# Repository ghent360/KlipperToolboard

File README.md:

# Huvud 3D Printer toolhead board
This is a modified version of the KilipperBoard started by bondus(https://github.com/bondus/KlipperToolboard). The goal is to make the board as cheap as possible. Removed the CAN interface, switched to RP4020 MCU since it is more available. Added extra IO pins for LEDs or other sensors.
# Original author words
A very small 3D printer board for use on a direct drive toolhead. It is designed to be used with Klipper firmware. Klipper has the awesome feature to be able to use multiple MCUs connected to the host over a (relatively) high latency connection.

Features: 
* One TMC2209 stepper driver for the extruder
* Three MOSFETs for fans
* One big MOSFET for the hotend heater
* Two thermistor inputs
* ADXL345 accelerometer for resonance testing
* Support for 3 endstops
* 3 extra I/O pins for RGB LEDs or other functions
* RP4020 Dual core 133MHz 32bit ARM MCU
* USB, for flashing firmware

Main power is 12-24V. 24V is preferred to keep the currents low

All done in KiCad and open source. 

If you are interesting in helping out, testing or eventually using this board feel free to contact me at ghent360@iqury.us.

### Documentation

* [Pinout and hook up](doc/pinout.md)
* [Klipper configuration](doc/klipper.md)
* [Prototype versions of the board](doc/versions.md)

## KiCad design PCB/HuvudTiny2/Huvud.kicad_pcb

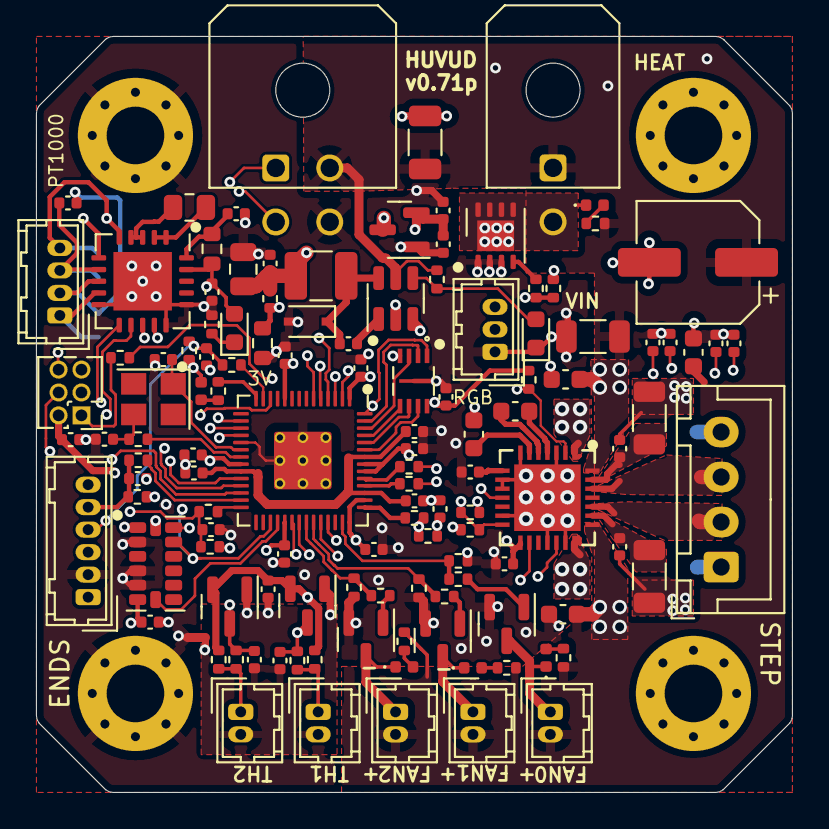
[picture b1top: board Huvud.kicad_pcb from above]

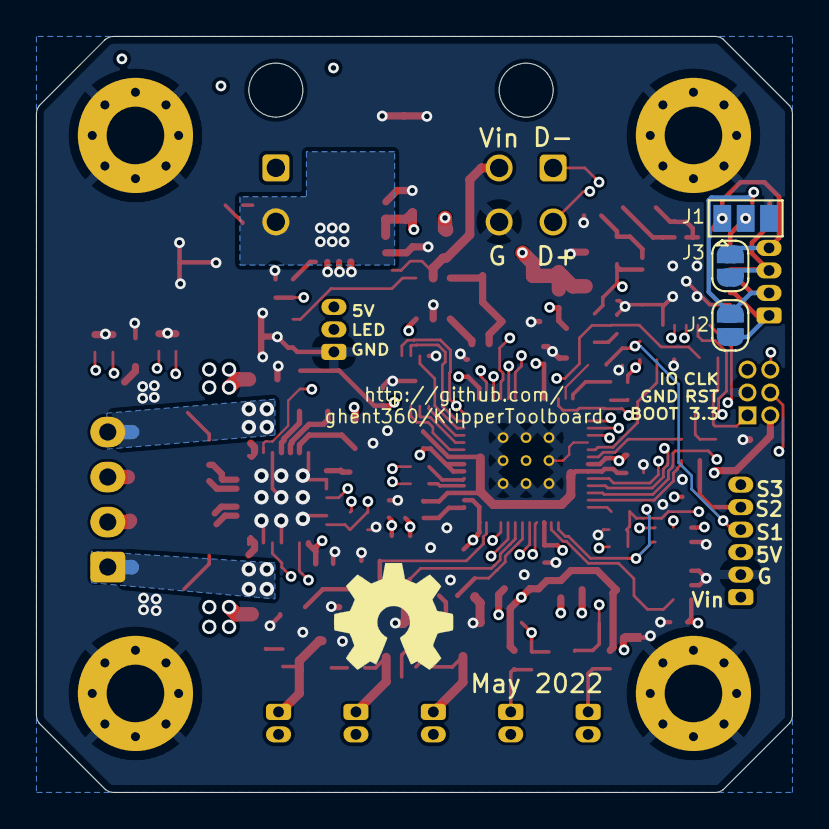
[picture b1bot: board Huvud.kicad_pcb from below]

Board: 4 copper layers, 42.0 x 42.0 mm, 129 parts (4 on the bottom side), 88 nets.

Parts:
C1, C2, C9, C10, C11, C19, C23, C24, C25, C27, C30, C31, C35, C37, C38, C39, C40, C41, C42, C43, C45: 0.1uF; C_0402_1005Metric
C3, C6, C7, C16: 0.1uF/35V; C_0603_1608Metric
C4, C17, C33, C34: 4.7uF; C_0402_1005Metric
C5: 22nf/50V; C_0603_1608Metric
C8: 100uF/35V; CP_Elec_6.3x7.7
C12, C13: 30pF; C_0402_1005Metric
C14, C22: 10uF/35V; C_1206_3216Metric
C15: 22uF; C_0805_2012Metric
C18, C32, C44: 2.2uF; C_0402_1005Metric
C20, C21, C26, C28: 1nF 50V; C_0402_1005Metric
C29, C36: 100nF; C_0402_1005Metric
D1, D2, D3, D5, D10: LEDGR; LED_0402_1005Metric
D4: 1N5819WS; D_SOD-323
D6, D8: LEDRED; LED_0603_1608Metric
D7, D9: BAT54S; SOT-23
FB1: 600 ohm; R_0603_1608Metric
H1, H2, H3, H4: MountingHole; MountingHole_3.2mm_M3_Pad_Via
J1: MOLEX Micro Fit 2x2; Molex_Micro-Fit_3.0_43045-0400_2x02_P3.00mm_Horizontal
J2: DBG; PinHeader_2x03_P1.27mm_Vertical
J3, J8: THERM; Hirose_DF13-02P-1.25DSA_1x02_P1.25mm_Vertical
J4: FAN1; Hirose_DF13-02P-1.25DSA_1x02_P1.25mm_Vertical
J5: FAN2; Hirose_DF13-02P-1.25DSA_1x02_P1.25mm_Vertical
J6: Heater; Molex_Micro-Fit_3.0_43045-0200_2x01_P3.00mm_Horizontal
J7: Endstop; Hirose_DF13-06P-1.25DSA_1x06_P1.25mm_Vertical
J9: STEPPER; JST_XH_B4B-XH-A_1x04_P2.50mm_Vertical
J10: FAN0; Hirose_DF13-02P-1.25DSA_1x02_P1.25mm_Vertical
J11: IO; Hirose_DF13-03P-1.25DSA_1x03_P1.25mm_Vertical
J12: Conn_01x04; Hirose_DF13-04P-1.25DSA_1x04_P1.25mm_Vertical
JP1: SolderJumper_3_Open; SolderJumper-3_P1.3mm_Open_Pad1.0x1.5mm
JP2, JP3: SolderJumper_2_Open; SolderJumper-2_P1.3mm_Open_RoundedPad1.0x1.5mm
L1: 6.8uH; L_1210_3225Metric
LOGO1: Logo_Open_Hardware_Small; OSHW-Symbol_6.7x6mm_SilkScreen
NT1: Net-Tie_2; NetTie-2_SMD_Pad0.5mm
Q1, Q2, Q4: AO3400A; SOT-23
Q3: AON7534; DFN-8-1EP_3x3mm_P0.65mm_EP1.7x2.05mm
R2, R9: 4.7k; R_0402_1005Metric
R3, R6, R16, R20, R30: 1k; R_0402_1005Metric
R4, R7: 0.1 1%; R_1206_3216Metric
R5, R8, R10, R12, R13, R14, R15, R17, R18, R19, R23, R24, R29, R32, R33, R36, R38, R42, R43: 10k; R_0402_1005Metric
R11: 400; R_0805_2012Metric
R21: 13k; R_0603_1608Metric
R22: 68k; R_0402_1005Metric
R25: 1; R_0402_1005Metric
R26: 200; R_0402_1005Metric
R27, R28, R34, R35: 22; R_0402_1005Metric
R31, R37: 27.4; R_0402_1005Metric
U1: ADXL345; LGA-14_3x5mm_P0.8mm_LayoutBorder1x6y
U2: TMC2209-LA; TMC22xx_QFN
U3: RP2040; RP2040-QFN-56
U4: EUP3458; SOT-23-6
U5: XC6206PxxxMR; SOT-23
U6: W25Q16JVUXIQ
U7: MAX31865xTP; TQFN-20-1EP_5x5mm_P0.65mm_EP3.25x3.25mm
Y1: 12MHz; Crystal_SMD_3225-4Pin_3.2x2.5mm

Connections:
+3V3: C9.2, C10.1, C11.2, C17.2, C23.2, C24.1, C34.2, C38.1, C39.1, C40.1, C41.1, C42.1, C43.1, C44.1, D5.2 (A), D8.2 (A), FB1.1, J2.2, R18.1, R19.1, R26.2, R32.1, R42.1, U1.1 (Vdd_I/O), U1.6 (Vs), U2.15 (VCC_IO), U3.1 (IOVDD), U3.10 (IOVDD), U3.22 (IOVDD), U3.33 (IOVDD), U3.42 (IOVDD), U3.44 (VREG_IN), U3.48 (USB_VDD), U3.49 (IOVDD), U5.2 (VO), U6.8 (VCC), U7.19 (DVDD)
+5V: C15.1, C33.2, J7.3, J11.3, L1.2, R22.2, U5.3 (VI)
/ADC_AVDD: R25.1, U3.43 (ADC_AVDD)
/D+: R31.1, U3.47 (USB_DP)
/D-: R37.1, U3.46 (USB_DM)
/QSPI_SCLK: U3.52 (QSPI_SCLK), U6.6 (CLK)
/QSPI_SD0: U3.53 (QSPI_SD0), U6.5 (DIIO0)
/QSPI_SD1: U3.55 (QSPI_SD1), U6.2 (DOIO1)
/QSPI_SD2: U3.54 (QSPI_SD2), U6.3 (/WPIO2)
/QSPI_SD3: U3.51 (QSPI_SD3), U6.7 (/HOLD)
/QSPI_SS: R6.1, U3.56 (QSPI_SS), U6.1 (/CS)
/ST_A1: C28.2, J9.2, U2.24 (OA1)
/ST_A2: C26.1, J9.1, U2.21 (OA2)
/ST_B1: C21.2, J9.3, U2.26 (OB1)
/ST_B2: C20.1, J9.4, U2.1 (OB2)
ACS: U1.7 (~CS), U3.32 (GPIO21)
AREF: C18.1, D7.2, D9.2, R2.2, R9.2, R25.2, R26.1
BOOT: J2.1, R6.2
BRA: C36.1, R4.2, U2.23 (BRA)
BRB: C29.1, R7.2, U2.27 (BRB)
ENDSTOP1: R33.2, U3.13 (GPIO10)
ENDSTOP2: R43.2, U3.27 (GPIO16)
ENDSTOP3: R36.2, U3.28 (GPIO17)
FAN0: R23.1, R27.1, U3.41 (GPIO29_ADC3)
FAN1: R8.2, R34.1, U3.37 (GPIO25)
FAN2: R10.1, R35.1, U3.36 (GPIO24)
GND: C2.2, C4.2, C6.2, C7.2, C8.2, C9.1, C10.2, C11.1, C12.1, C13.1, C14.1, C15.2, C16.2, C17.1, C20.2, C21.1, C22.1, C23.1, C24.2, C26.2, C27.1, C28.1, C29.2, C30.2, C31.2, C32.2, C33.1, C34.1, C35.2, C36.2, C37.2, C38.2, C39.2, C40.2, C41.2, C42.2, C43.2, C44.2, D4.2 (A), D6.1 (K), H1.1, H2.1, H3.1, H4.1, J1.4, J2.3, J7.2, J11.1, JP1.3 (B), NT1.1, Q1.2 (S), Q2.2 (S), Q3.1 (S), Q4.2 (S), R4.1, R7.1, R8.1, R10.2, R12.2, R20.2, R21.2, R23.2, R24.1, U1.2 (GND), U1.4 (GND), U1.5 (GND), U2.3 (GND), U2.7 (SPREAD), U2.9 (MS1_AD0), U2.10 (MS2_AD1), U2.13 (CLK), U2.18 (GND), U2.20 (STDBY), U2.29 (EPAD), U3.19 (TESTEN), U3.57 (GND), U4.2 (GND), U5.1 (GND), U6.4 (GND), U6.9 (EPAD), U7.10 (GND), U7.15 (DGND), U7.16 (GND), U7.21 (GND)
GNDA: C1.1, C18.2, C25.1, D7.1, D9.1, J3.2, J8.2, NT1.2
HEATER: R12.1, R28.1, U3.4 (GPIO2)
IO4: J11.2, U3.6 (GPIO4)
LED0: R3.1, U3.14 (GPIO11)
MCS: U3.12 (GPIO9), U7.13 (~CS)
NRST: J2.4, U3.26 (RUN)
unnamed: C12.2, R30.1, Y1.3
unnamed: D1.2 (A), R13.2
unnamed: D1.1 (K), J4.1, Q1.3 (D)
unnamed: D2.2 (A), R14.2
unnamed: D2.1 (K), J5.1, Q2.3 (D)
unnamed: D3.2 (A), R15.2
unnamed: D3.1 (K), J6.2, Q3.3 (D)
unnamed: C19.2, D4.1 (K), L1.1, U4.6 (SW)
unnamed: D5.1 (K), R3.2
unnamed: D6.2 (A), R38.2, U4.4 (EN)
unnamed: D8.1 (K), R20.1
unnamed: D10.2 (A), R29.2
unnamed: D10.1 (K), J10.1, Q4.3 (D)
unnamed: J3.1, R2.1, R5.2
unnamed: C30.1, J7.4, R32.2, R33.1
unnamed: C31.1, J7.5, R42.2, R43.1
unnamed: C2.1, J7.6, R19.2, R36.1
unnamed: J8.1, R9.1, R17.2
unnamed: J12.1, JP3.1 (A), U7.9 (FORCE-)
unnamed: C45.1, J12.2, JP3.2 (B), U7.8 (RTDIN-)
unnamed: C45.2, J12.3, JP2.1 (A), U7.7 (RTDIN+)
unnamed: J12.4, JP1.1 (A), JP2.2 (B), U7.5 (FORCE+)
unnamed: JP1.2 (C), U7.6 (FORCE2)
unnamed: Q1.1 (G), R34.2
unnamed: Q2.1 (G), R35.2
unnamed: Q3.2 (G), R28.2
unnamed: Q4.1 (G), R27.2
unnamed: C4.1, U2.8 (5VOUT)
unnamed: C5.1, U2.5 (CPI)
unnamed: C5.2, U2.4 (CPO)
unnamed: C3.1, U2.6 (VCP)
unnamed: C32.1, C35.1, C37.1, U3.23 (DVDD), U3.45 (VREG_VOUT), U3.50 (DVDD)
unnamed: C13.2, U3.20 (XIN), Y1.1
unnamed: R30.2, U3.21 (XOUT)
unnamed: C19.1, U4.1 (BST)
unnamed: R21.1, R22.1, U4.3 (FB)
unnamed: R11.1, U7.1 (BIAS), U7.2 (REFIN+)
unnamed: R11.2, U7.3 (REFIN-), U7.4 (ISENSOR)
unnamed: C27.2, FB1.2, U7.20 (VDD)
SCL: U1.14 (SCL/SCLK), U3.34 (GPIO22), U7.12 (SCLK)
SDI: U1.13 (SDA/SDI/SDIO), U3.35 (GPIO23), U7.11 (SDI)
SDO: U1.12 (SDO/ADDR), U3.31 (GPIO20), U7.14 (SDO)
ST_DIAG: U2.11 (DIAG), U3.16 (GPIO13)
ST_DIR: U2.19 (DIR), U3.17 (GPIO14)
ST_EN: R18.2, U2.2 (ENN), U3.5 (GPIO3)
ST_STEP: U2.16 (STEP), U3.18 (GPIO15)
ST_UART_RX: R16.2, R24.2, U2.14 (PDN_UART), U3.3 (GPIO1)
ST_UART_TX: R16.1, U3.2 (GPIO0)
ST_VS: C3.2, C6.1, C7.1, C8.1, C14.2, C16.1, C22.2, J1.2, J4.2, J5.2, J6.1, J7.1, J10.2, R13.1, R14.1, R15.1, R29.1, R38.1, U2.22 (VS), U2.28 (VS), U4.5 (Vin)
SWCLK: J2.6, U3.24 (SWCLK)
SWDIO: J2.5, U3.25 (SWD)
THERM1: C25.2, D9.3, R5.1, U3.39 (GPIO27_ADC1)
THERM2: C1.2, D7.3, R17.1, U3.38 (GPIO26_ADC0)
USBD+: J1.3, R31.2
USBD-: J1.1, R37.2

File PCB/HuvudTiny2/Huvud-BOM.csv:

Comment,Designator,Footprint,LCSC, LCSC
"15pF","C12,C13","Capacitor_SMD:C_0402_1005Metric","","C1548"
"22uF","C14,C15,C32","Capacitor_SMD:C_0805_2012Metric","","C45783"
"1uF","C18","Capacitor_SMD:C_0402_1005Metric","","C52923"
"0.1uF","C2,C9,C10,C11,C19,C24,C25,C30,C31","Capacitor_SMD:C_0402_1005Metric","","C1525"
"1nF 50V","C20,C21,C26,C28","Capacitor_SMD:C_0402_1005Metric","","C1523"
"10uF/35V","C22","Capacitor_SMD:C_1206_3216Metric","","C13585"
"10uF","C23,C27","Capacitor_SMD:C_0402_1005Metric","","C15525"
"100nF","C29,C36","Capacitor_SMD:C_0402_1005Metric","","C1525"
"0.1uF/35V","C3,C6,C7,C16","Capacitor_SMD:C_0603_1608Metric","","C14663"
"4.7uF","C4,C33,C34,C35","Capacitor_SMD:C_0402_1005Metric","","C23733"
"22nf/50V","C5","Capacitor_SMD:C_0603_1608Metric","","C21122"
"100uF/35V","C8","Capacitor_SMD:CP_Elec_6.3x7.7","","C134792"
"LEDGR","D1,D2,D3,D5","LED_SMD:LED_0402_1005Metric","","C130723"
"PMEG6010CEJ","D4","Diode_SMD:D_SOD-323F","","C406049"
"LEDRED","D6,D8","LED_SMD:LED_0603_1608Metric","","C2286"
"BAT54S","D9","Package_TO_SOT_SMD:SOT-23","","C12765"
"MountingHole","H1,H2,H3,H4","MountingHole:MountingHole_3.2mm_M3_Pad_Via",""
"Vin","J1","Huvud:TerminalBlock_TE_282834-2_1x02_P2.54mm_Horizontal","","C557685"
"USB_Micro-B","J12","Huvud:MC-101C","","C183609"
"DBG","J2","Connector_PinHeader_2.54mm:PinHeader_2x03_P2.54mm_Vertical","","C402781"
"THERM","J3","Connector_JST:JST_PH_B2B-PH-K_1x02_P2.00mm_Vertical","","C225188"
"FAN0","J4","Connector_JST:JST_PH_B2B-PH-K_1x02_P2.00mm_Vertical","","C225188"
"FAN1","J5","Connector_JST:JST_PH_B2B-PH-K_1x02_P2.00mm_Vertical","","C225188"
"Heater","J6","Huvud:TerminalBlock_TE_282834-2_1x02_P2.54mm_Horizontal","","C557685"
"Endstop","J7","Connector_JST:JST_PH_B5B-PH-K_1x05_P2.00mm_Vertical","","C225191"
"STEPPER","J9","Connector_JST:JST_XH_B4B-XH-A_1x04_P2.50mm_Vertical","","C492489"
"22uH","L1","Inductor_SMD:L_0805_2012Metric","","C32375"
"Logo_Open_Hardware_Small","LOGO1","Symbol:OSHW-Symbol_6.7x6mm_SilkScreen",""
"Net-Tie_2","NT1","NetTie:NetTie-2_SMD_Pad0.5mm",""
"AO3400A","Q1,Q2","Package_TO_SOT_SMD:SOT-23","","C20917"
"AON7534","Q3","Huvud:DFN-8-1EP_3x3mm_P0.65mm_EP1.7x2.05mm","","C115844"
"10k","R1,R5,R8,R10,R11,R12,R13,R14,R15,R18,R19,R21,R22,R24,R32,R33,R36,R42,R43","Resistor_SMD:R_0402_1005Metric","","C25744"
"4.7k","R2","Resistor_SMD:R_0402_1005Metric","","C25900"
"22","R25,R26,R28,R34,R35","Resistor_SMD:R_0402_1005Metric","","C25092"
"470","R3,R20","Resistor_SMD:R_0402_1005Metric","","C25117"
"0.1 1%","R4,R7","Resistor_SMD:R_1206_3216Metric","","C25334"
"1k","R6,R16","Resistor_SMD:R_0402_1005Metric","","C11702"
"ADXL345","U1","Package_LGA:LGA-14_3x5mm_P0.8mm_LayoutBorder1x6y","","C9667"
"TMC2209-LA","U2","Huvud:TMC22xx_QFN","","C465949 "
"ATSAMD21E15B-M","U3","Package_DFN_QFN:QFN-32-1EP_5x5mm_P0.5mm_EP3.6x3.6mm",""
"XC6206PxxxMR","U4","Package_TO_SOT_SMD:SOT-23","","C5446"
"32k","Y1","Crystal:Crystal_SMD_3215-2Pin_3.2x1.5mm","","C32346"

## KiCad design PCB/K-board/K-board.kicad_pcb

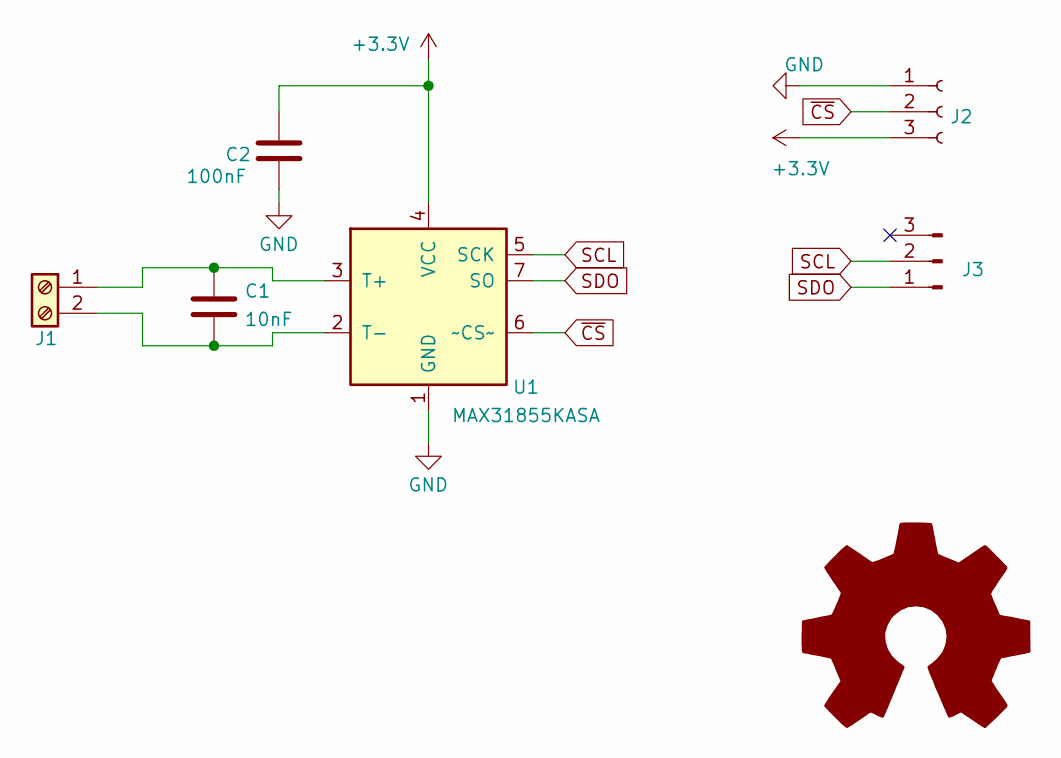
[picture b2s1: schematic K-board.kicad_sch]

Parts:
C1: 10nF; C_0402_1005Metric; LCSC C15195
C2: 100nF; C_0402_1005Metric; LCSC C1525
J1: Screw_Terminal_01x02; TerminalBlock_Phoenix_PT-1,5-2-3.5-H_1x02_P3.50mm_Horizontal
J2: Conn_01x03_Female; PinSocket_1x03_P1.27mm_Vertical
J3: Conn_01x03_Male; PinHeader_1x03_P1.27mm_Vertical
U1: MAX31855KASA; SOIC-8_3.9x4.9mm_P1.27mm; LCSC C52028

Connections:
+3V3: C2.1, J2.3, U1.4 (VCC)
GND: C2.2, J2.1, U1.1 (GND)
unnamed: C1.1, J1.1, U1.3 (T+)
unnamed: C1.2, J1.2, U1.2 (T-)
SCL: J3.2, U1.5 (SCK)
SDO: J3.1, U1.7 (SO)
~CS: J2.2, U1.6 (~CS~)

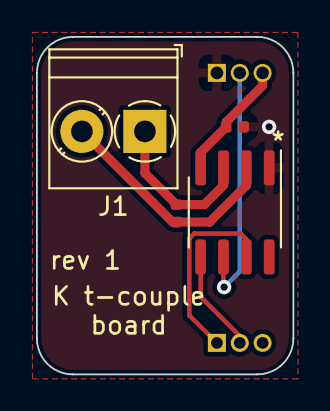
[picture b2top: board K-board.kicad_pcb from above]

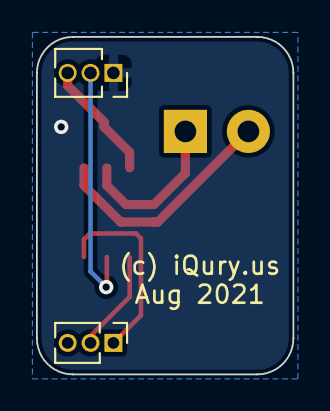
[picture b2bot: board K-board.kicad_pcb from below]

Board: 2 copper layers, 14.2 x 18.8 mm, 6 parts (2 on the bottom side), 7 nets.

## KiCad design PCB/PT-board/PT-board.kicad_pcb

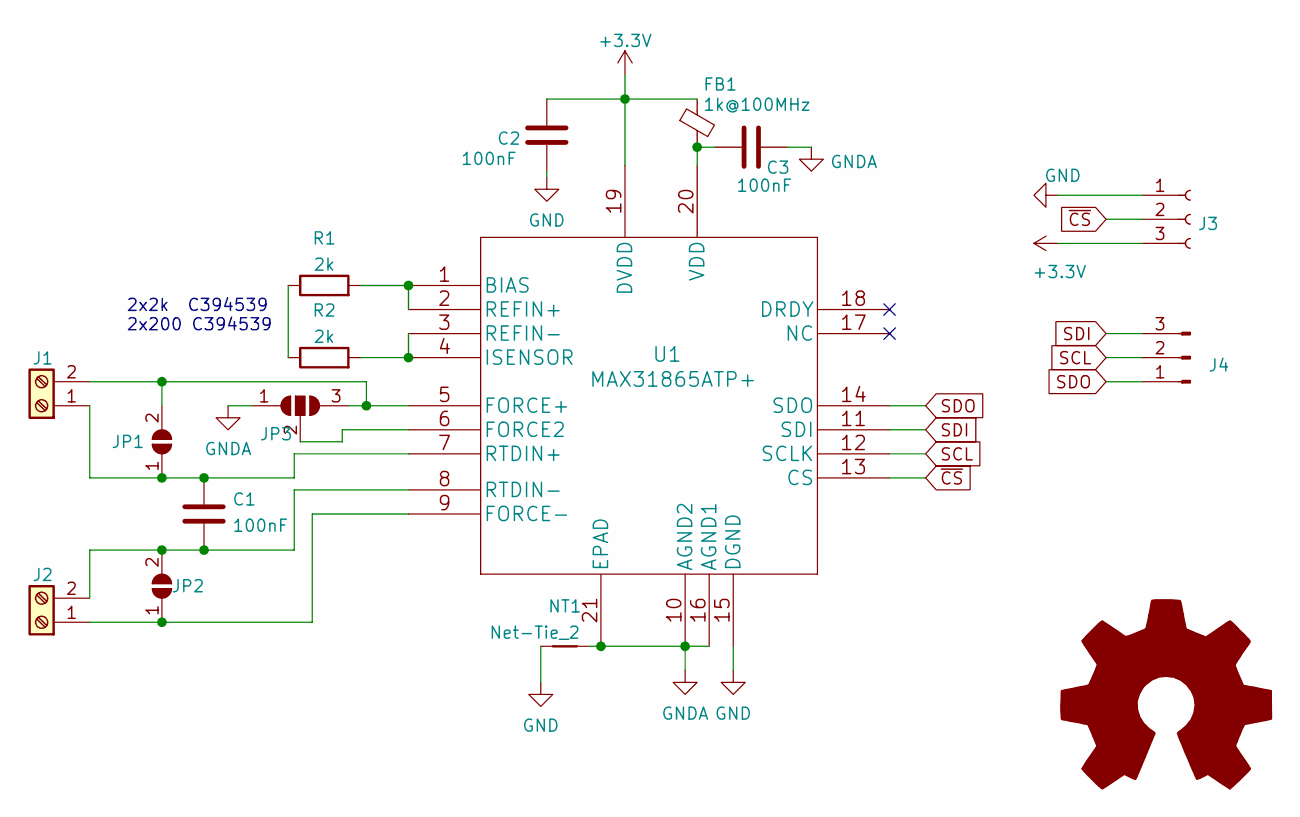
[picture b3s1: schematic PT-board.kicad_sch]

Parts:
C1, C2, C3: 100nF; C_0402_1005Metric; LCSC C1525
FB1: 1k@100MHz; L_0402_1005Metric; LCSC C85819
J1, J2: Screw_Terminal_01x02; TerminalBlock_Phoenix_PT-1,5-2-3.5-H_1x02_P3.50mm_Horizontal
J3: Conn_01x03_Female; PinSocket_1x03_P1.27mm_Vertical
J4: Conn_01x03_Male; PinHeader_1x03_P1.27mm_Vertical
JP1, JP2: SolderJumper_2_Open; SolderJumper-2_P1.3mm_Open_TrianglePad1.0x1.5mm
JP3: SolderJumper_3_Open; SolderJumper-3_P1.3mm_Open_RoundedPad1.0x1.5mm_NumberLabels
NT1: Net-Tie_2; NetTie-2_SMD_Pad0.5mm
R1, R2: 2k; R_0603_1608Metric; LCSC C394539
U1: MAX31865ATP+; MAX31865ATP

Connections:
+3V3: C2.1, FB1.1, J3.3, U1.19 (DVDD)
GND: C2.2, J3.1, NT1.1, U1.15 (DGND)
GNDA: C3.2, JP3.1 (A), NT1.2, U1.10 (AGND2), U1.16 (AGND1), U1.21 (EPAD)
unnamed: C1.1, J1.1, JP1.1 (A), U1.7 (RTDIN+)
unnamed: C1.2, J2.2, JP2.2 (B), U1.8 (RTDIN-)
unnamed: C3.1, FB1.2, U1.20 (VDD)
unnamed: J1.2, JP1.2 (B), JP3.3 (B), U1.5 (FORCE+)
unnamed: J2.1, JP2.1 (A), U1.9 (FORCE-)
unnamed: JP3.2 (C), U1.6 (FORCE2)
unnamed: R1.1, R2.1
unnamed: R1.2, U1.1 (BIAS), U1.2 (REFIN+)
unnamed: R2.2, U1.3 (REFIN-), U1.4 (ISENSOR)
SCL: J4.2, U1.12 (SCLK)
SDI: J4.3, U1.11 (SDI)
SDO: J4.1, U1.14 (SDO)
~CS: J3.2, U1.13 (CS)

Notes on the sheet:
2x2k C394539 2x200 C394539

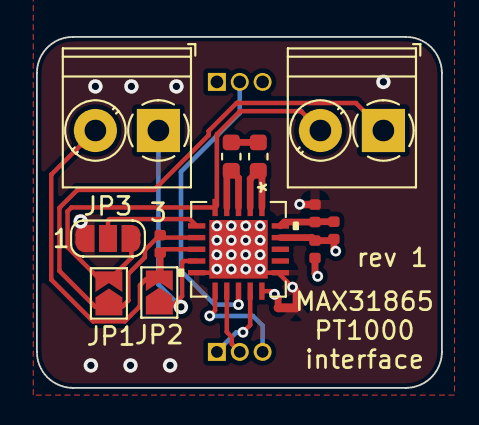
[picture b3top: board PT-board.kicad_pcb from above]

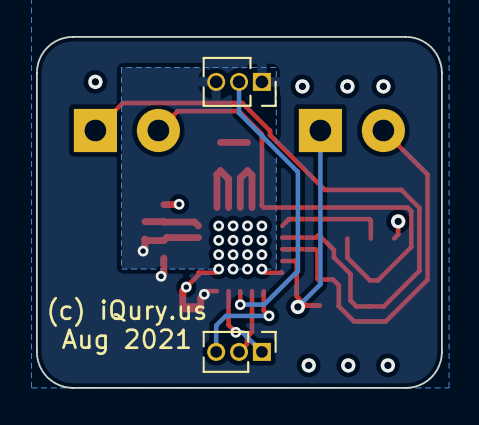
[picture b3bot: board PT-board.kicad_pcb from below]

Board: 4 copper layers, 22.5 x 19.5 mm, 15 parts (2 on the bottom side), 16 nets.

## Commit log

2021-05-17 Convert to Kicad 6.
2021-05-17 Power from USB, remove CAN. Update micro USB footprint. Update TMC footprint.
2021-05-22 Improve power routing. Fix TH input protection.
2021-05-22 Generated gerber files.
2021-05-24 Add all R1 files - sent to fab.
2021-05-24 Make C8 label invisible on PCB.
2021-05-24 Removed old board variants. Updated the readme.
2021-05-24 Add protection diode on endstop 1. Add back heatsink for power mosfet.
2021-05-24 Add gitignore file.
2021-05-25 Update sense resistors to 0.1 1206 size.
2021-05-25 Route VCC_IO to GPIO pin so we can reset the stepper driver.
2021-07-05 Added caps across stepper pins.
2021-07-05 Add caps across current sense resistors.
2021-07-05 Small tweaks to footprints.
2021-07-06 Fix typo.
2021-07-12 Replaced MCU with SAMD21
2021-07-12 Revert "Replaced MCU with SAMD21"
    This reverts commit 6913cf5f2b8e074e8779f2b10200d6d4802eef29.
2021-07-12 Some routing.
2021-07-12 Routing complete.
2021-07-12 Routed with 32k crystal.
2021-07-26 Update PCB routing.
2021-07-26 Update routing.
2021-07-31 Genedare manufacturing files. Send to fab. Make sligh routing mods after the fab output.
2021-08-01 Layout improvements.
2021-08-11 Flipped FAN connectors. Changed pinout on endstop connector. Added SPI thermocouple connector - shared CS with THERMISTOR.
2021-08-11 Round PCB corners.
2021-08-13 Add PT1000 board.
2021-08-13 Update PT board size and move filter cap on the Huvud so ethe two boards can actually be attached together.
2021-08-13 Added K-type thermocouple board based on MAX31855.
2021-08-23 Improve sense resistor ground. Improve power mosfer routing. Set PCB color and copper finish.
2021-09-11 Route new version with 1.25mm connectors. Added TH2 and 24V on the endstop connector.
2021-09-17 Switched power & USB to MOLEX MicroFit 2x6. Switched heater to 3.5mm terminal.
2021-09-17 Updated GNDA layout.
2021-09-24 Added power regulator 24V->5V. Changed molex to 2x2
2021-09-24 Update screw terminal to molex connector.
2021-09-26 Finished routing.
2021-09-26 Clean PCB routing.
2021-09-26 Remove all traces this time for real.
2021-09-26 Stepper power routed.
2021-09-26 Routed all traces.
2021-09-26 Improve layout.
2021-10-01 Add third fan mosfet (could be used for lighing).
2021-10-09 LDO power supply from 24V.
2021-10-10 Re work power supply added 5V stage: 24v->5V->3.3V
2021-10-10 Resolve DRC warnings.
2021-10-10 Add LCSC component for the MCU.
2021-10-10 Update fabrication files.
2021-10-10 Update PCB to match with schematics metadata. Re generate interactive BOM.
2022-01-06 Add RP2040 libraries.
2022-01-06 Added footprint libraries.
2022-01-06 Remove SAMD21 part update chrystal to 12MHz.
2022-01-06 Add SPI flash symbol.
2022-01-06 Add flash 3d model.
2022-01-06 Update TMC symbol.
2022-01-06 Added RP2040 and hooked power, USB and analog in the schematics.
2022-01-06 Almost all components are on the board.
2022-01-07 Fully routed. Some 3D models are messed up.
2022-03-02 Add new buck cvtr as power supply. Re-route the board.
2022-03-27 Updated silk screen. Added soem extra GND vias. Updated 3D models.
2022-03-27 Updated readme.
2022-03-30 Improve GND connection on some components.
2022-04-18 Add PT100 reader.
2022-04-18 re-layout the board to accomodate the PT100 reader chip.
2022-04-24 Updated some traces, fixed minor DRC issues.
2022-04-24 Placed all components. Routed some more traces.
2022-05-01 Update 3d model paths.
2022-05-01 Fix all 3d models. DRC passes.

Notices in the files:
parts and their libraries:
Copyright 2021 Accelerated Designs. All rights reserved.
